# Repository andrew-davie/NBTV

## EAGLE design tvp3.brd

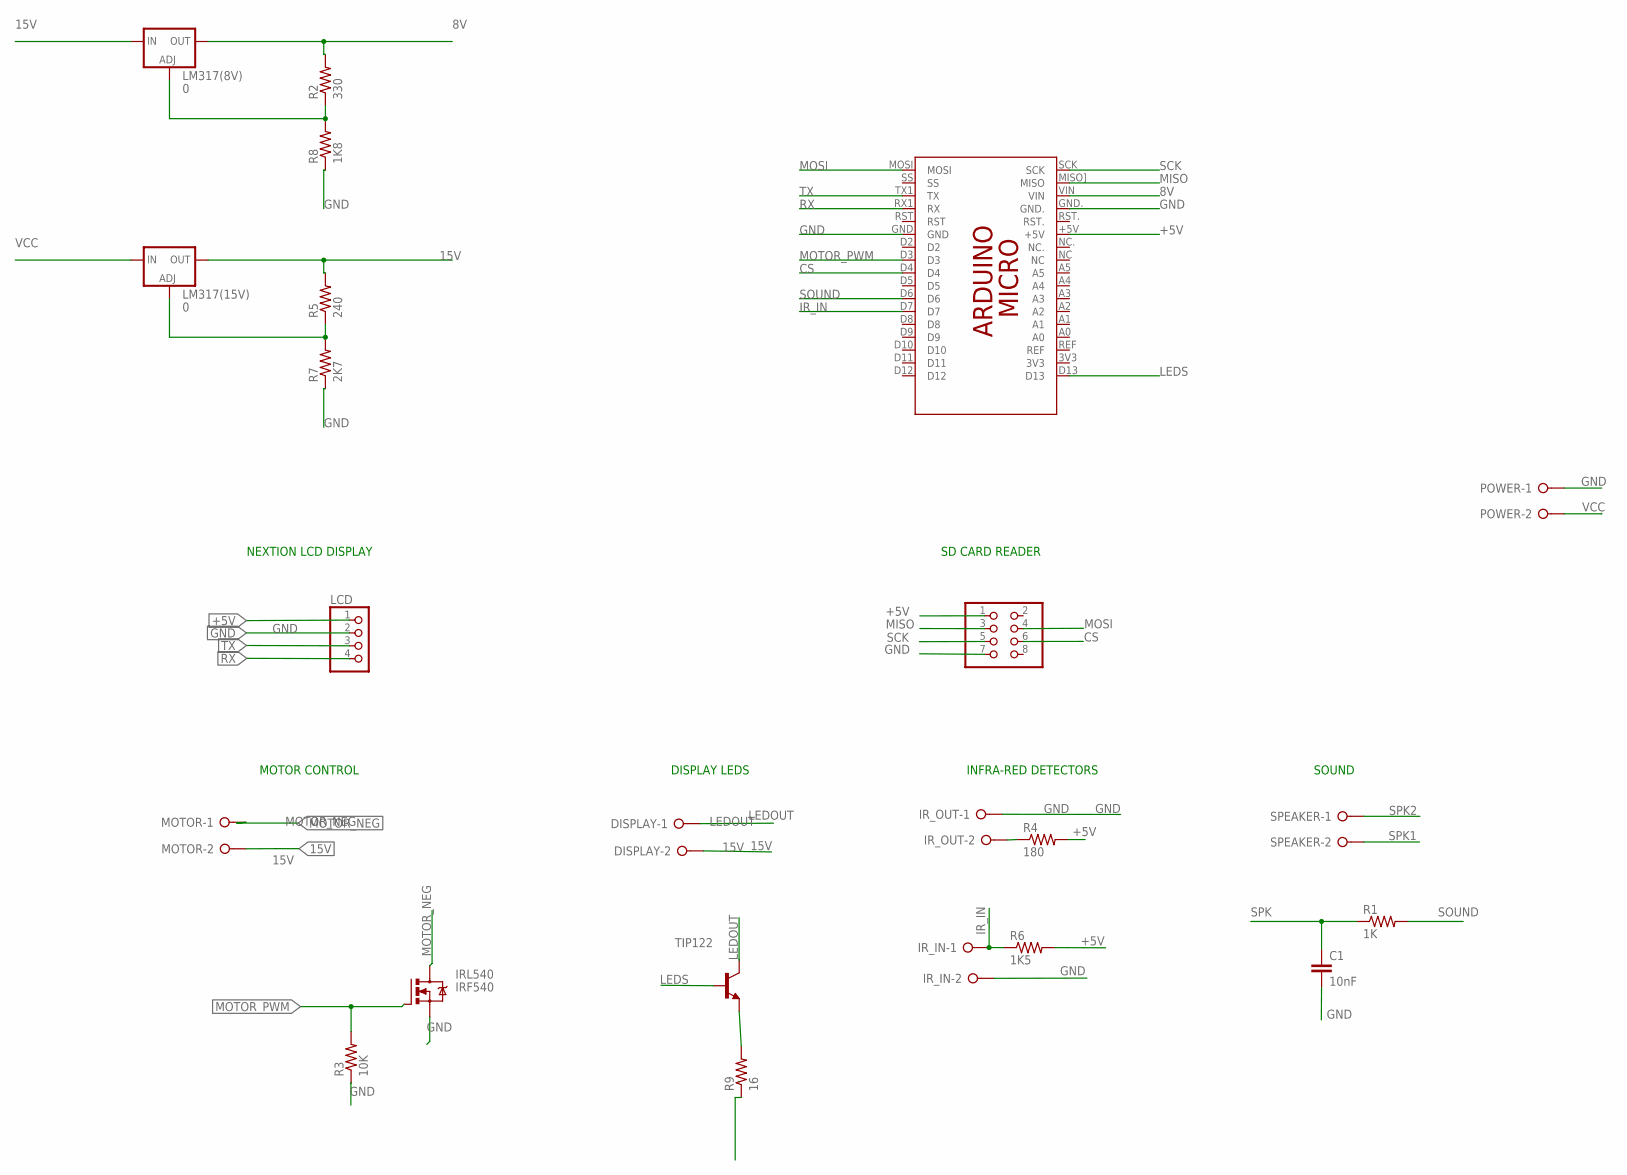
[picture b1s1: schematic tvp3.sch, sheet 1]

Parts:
C1: 10nF; C2.5-2
DISPLAY: W237-02P; W237-132
IRL540: IRF540; TO220BV
IR_IN: W237-02P; W237-132
IR_OUT: W237-02P; W237-132
LCD: PINHD-1X4; 1X04
LM317(8V), LM317(15V): 0; 317TS
MOTOR: W237-02P; W237-132
PCB2: ARDUINO_MICRO
POWER: W237-02P; W237-132
R1: 1K; 0207/10
R2: 330; 0207/10
R3: 10K; 0207/10
R4: 180; 0207/10
R5: 240; 0207/10
R6: 1K5; 0207/10
R7: 2K7; 0207/10
R8: 1K8; 0207/10
R9: 16; 0207/10
SPEAKER: W237-02P; W237-132
TIP122: -NPN-TO220V; TO220V
_: PINHD-2X4; 2X04

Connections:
8V: LM317(8V).2 (OUT), PCB2.VIN, R2.2
15V: DISPLAY.2, LM317(8V).3 (IN), LM317(15V).2 (OUT), MOTOR.2, R5.2
+5V: LCD.1, PCB2.+5V, R4.2, R6.2, _.1; also elsewhere on the board
CS: PCB2.D4, _.6
GND: C1.2, IRL540.S, IR_IN.2, IR_OUT.1, LCD.2, PCB2.GND, PCB2.GND., POWER.1, R3.1, R7.1, R8.1, R9.1, _.7; also elsewhere on the board
IR_IN: IR_IN.1, PCB2.D7, R6.1
IR_OUT: IR_OUT.2, R4.1
LEDOUT: DISPLAY.1, TIP122.2 (C)
LEDS: PCB2.D13, TIP122.1 (B)
MISO: PCB2.MISO] (MISO), _.3
MOSI: PCB2.MOSI, _.4
MOTOR_NEG: IRL540.D, MOTOR.1
MOTOR_PWM: IRL540.G, PCB2.D3, R3.2
unnamed: LM317(15V).1 (ADJ), R5.1, R7.2
unnamed: R9.2, TIP122.3 (E)
unnamed: LM317(8V).1 (ADJ), R2.1, R8.2
RX: LCD.4, PCB2.RX1 (RX)
SCK: PCB2.SCK, _.5
SOUND: PCB2.D6, R1.2
SPK: C1.1, R1.1; also elsewhere on the board
SPK1: SPEAKER.2; also elsewhere on the board
SPK2: SPEAKER.1; also elsewhere on the board
TX: LCD.3, PCB2.TX1 (TX)
VCC: LM317(15V).3 (IN), POWER.2

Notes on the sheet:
MOTOR CONTROL
DISPLAY LEDS
INFRA-RED DETECTORS
NEXTION LCD DISPLAY
SD CARD READER
SOUND

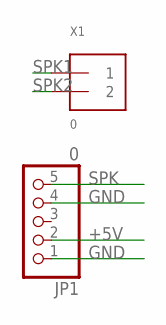
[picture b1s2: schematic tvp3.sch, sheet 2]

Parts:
JP1: 0; 1X05_ROUND_70
X1: 0; TERMBLOCK_1X2-3.5MM

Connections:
+5V: JP1.2; also elsewhere on the board
GND: JP1.1, JP1.4; also elsewhere on the board
SPK: JP1.5; also elsewhere on the board
SPK1: X1.1; also elsewhere on the board
SPK2: X1.2; also elsewhere on the board

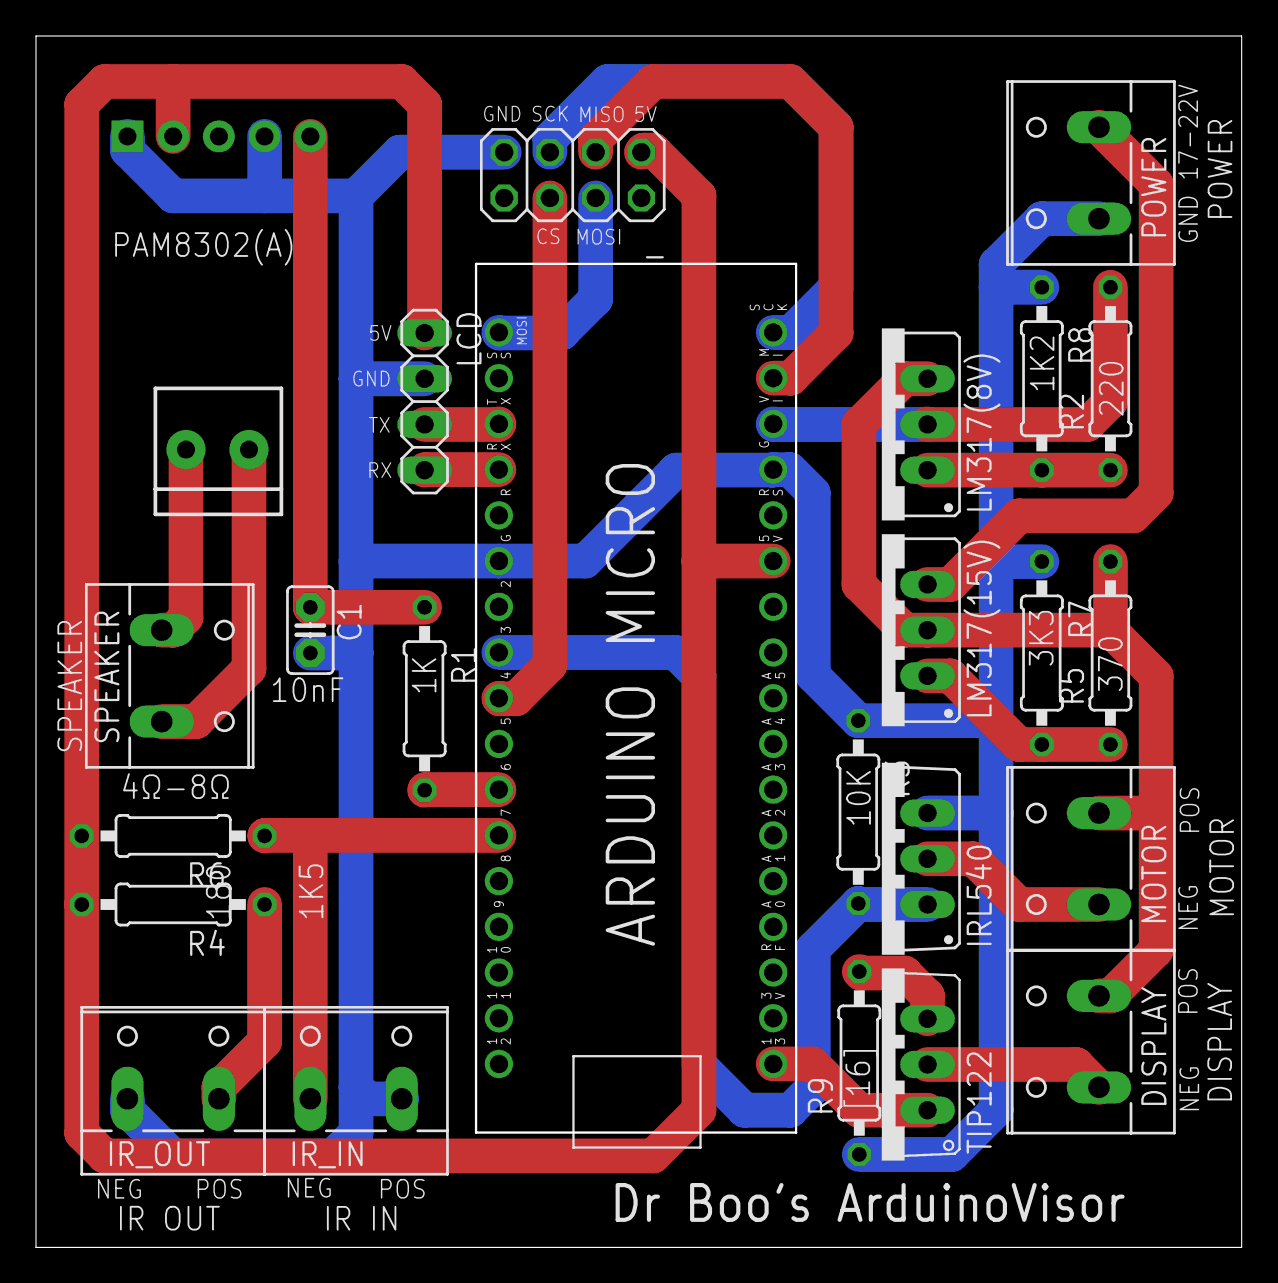
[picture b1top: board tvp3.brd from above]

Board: 2 copper layers, 67.0 x 67.3 mm, 25 parts (0 on the bottom side), 24 nets.

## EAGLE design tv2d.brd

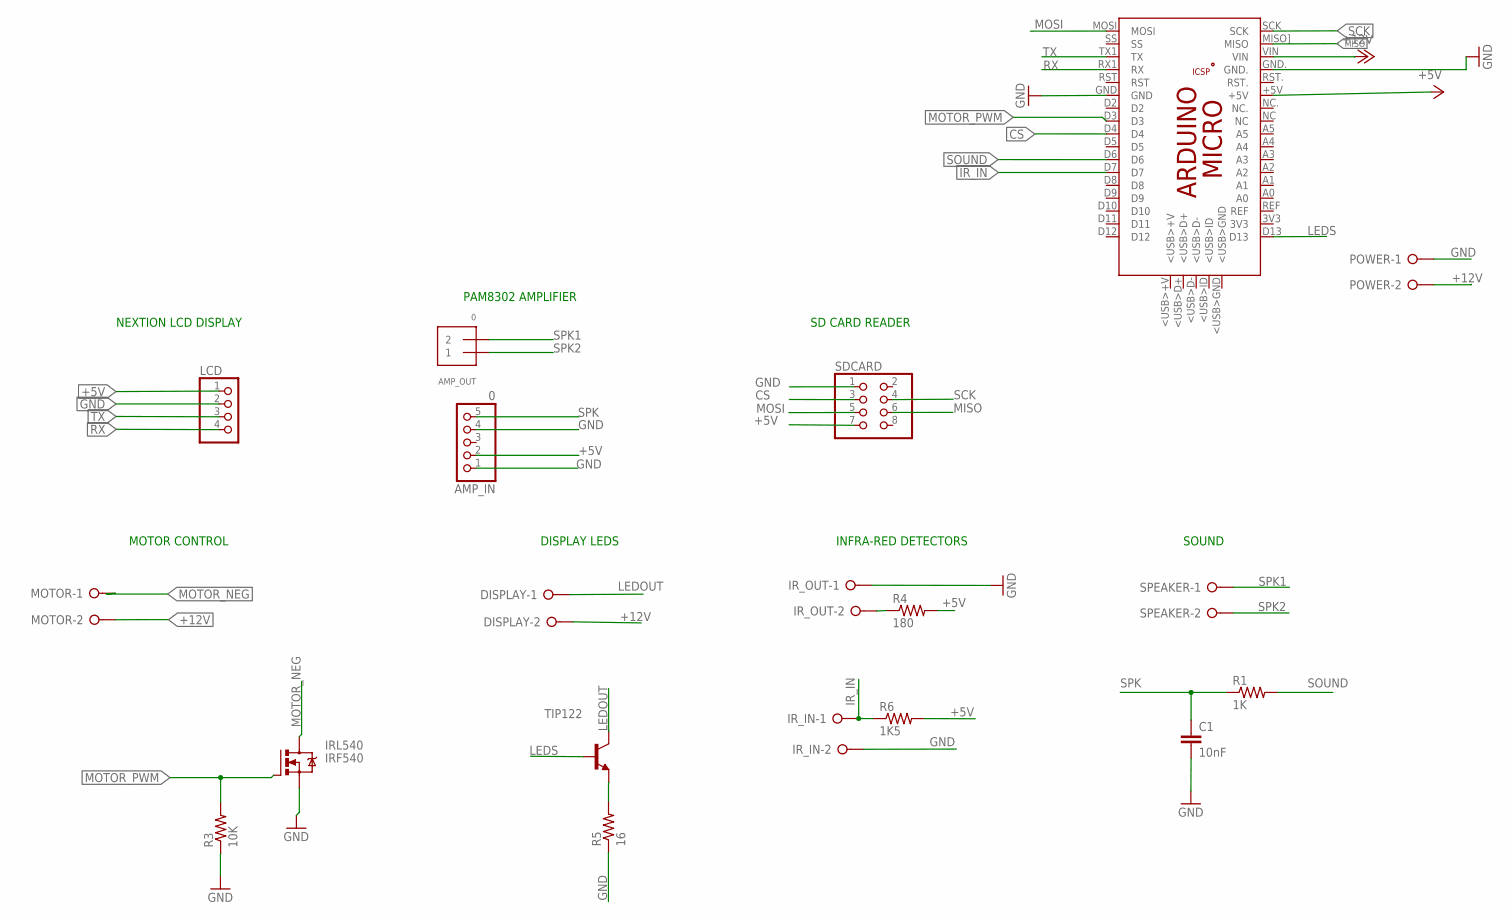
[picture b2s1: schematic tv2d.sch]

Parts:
AMP_IN: 0; 1X05_ROUND_70
AMP_OUT: 0; TERMBLOCK_1X2-3.5MM
C1: 10nF; C2.5-2
DISPLAY: W237-02P; W237-132
IRL540: IRF540; TO220BV
IR_IN: W237-02P; W237-132
IR_OUT: W237-02P; W237-132
LCD: PINHD-1X4; 1X04
MOTOR: W237-02P; W237-132
PCB1: ARDUINO_MICRO
POWER: W237-02P; W237-132
R1: 1K; 0207/10
R3: 10K; 0207/10
R4: 180; 0207/10
R5: 16; 0207/10
R6: 1K5; 0207/10
SDCARD: PINHD-2X4; 2X04
SPEAKER: W237-02P; W237-132
TIP122: -NPN-TO220V; TO220V

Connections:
+5V: AMP_IN.2, LCD.1, PCB1.+5V, R4.2, R6.2, SDCARD.7
+12V: DISPLAY.2, MOTOR.2, PCB1.VIN, POWER.2
CS: PCB1.D4, SDCARD.3
GND: AMP_IN.1, AMP_IN.4, C1.2, IRL540.S, IR_IN.2, IR_OUT.1, LCD.2, PCB1.GND, PCB1.GND., POWER.1, R3.1, R5.1, SDCARD.1
IR_IN: IR_IN.1, PCB1.D7, R6.1
IR_OUT: IR_OUT.2, R4.1
LEDOUT: DISPLAY.1, TIP122.2 (C)
LEDS: PCB1.D13, TIP122.1 (B)
MISO: PCB1.MISO] (MISO), SDCARD.6
MOSI: PCB1.MOSI, SDCARD.5
MOTOR_NEG: IRL540.D, MOTOR.1
MOTOR_PWM: IRL540.G, PCB1.D3, R3.2
unnamed: R5.2, TIP122.3 (E)
RX: LCD.4, PCB1.RX1 (RX)
SCK: PCB1.SCK, SDCARD.4
SOUND: PCB1.D6, R1.2
SPK: AMP_IN.5, C1.1, R1.1
SPK1: AMP_OUT.2, SPEAKER.1
SPK2: AMP_OUT.1, SPEAKER.2
TX: LCD.3, PCB1.TX1 (TX)

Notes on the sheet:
MOTOR CONTROL
DISPLAY LEDS
INFRA-RED DETECTORS
NEXTION LCD DISPLAY
PAM8302 AMPLIFIER
SD CARD READER
SOUND

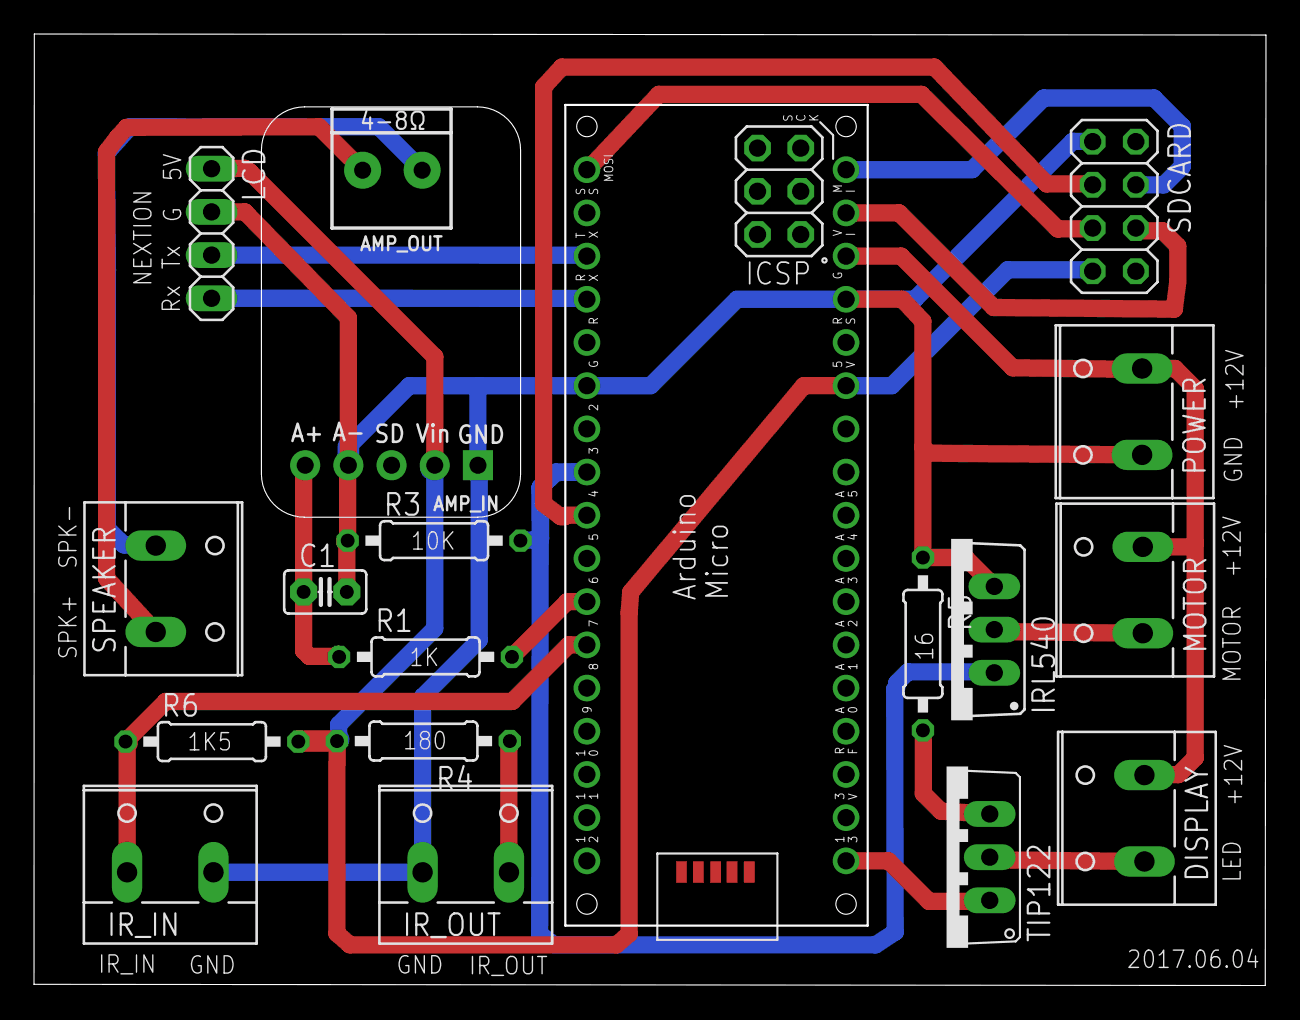
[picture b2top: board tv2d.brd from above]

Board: 2 copper layers, 72.4 x 55.9 mm, 19 parts (0 on the bottom side), 20 nets.

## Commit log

2017-03-10 first version
2017-03-25 let's get serious
    CIrcular streaming audio/video buffer implemented to reduce memory footprint
    my televisor is "pulling" and there must be a motor or disc bearing problem.
    PID operational but hardly able to resist the disturbance
    video streaming basically OK but occasonal glitching so there's a bug there somewhere
    SD card streaming good, but need a super-fast card, as we can't afford delays/lag
    rudimentary televisor operates OK off this code
2017-03-25 consolidation - prelminary
2017-03-25 cleaning for the great unwashed
2017-03-26 tidy up
2017-03-31 changed buffer handling
    playback pointer now absolute and continues regardless. Stream pointer also absolute, so calculation of bytes to stream is simple. The streaming might delay but will eventually catch up, and then the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
2017-04-01 gamma correction
2017-04-01 quadratic gamma correction from Klaas Robers
2017-04-04 8-bit video format, WAV loader rewrite
    now COmpatible with 16-bit and 8-bit NBTV files.
2017-04-05 some work on the Nextion interface
    lots of optimisation to reduce ram/memory
    fixed an off-by-one bug in the video playback (explains a few things)
    Nextion support works but clashes with playback - one or the other at the moment
    memory is short (RAM). May need to customise the libraries
2017-04-06 UI functional
    Moved video buffer stuffer to an interrupt, freeing up the main loop which now does the serial comms to the Nextion. This update has the 'brightness' control functional, taking slider values from the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
2017-04-10 functional frame lock
    First version demonstrating frame lock. Very slow and sensitive, but working!
2017-04-14 "solved" nextion RAM problem
    see NextionUI.cpp for comments - there appears to be an Arduino IDE linker problem.
2017-04-16 rationalisation
    Bug regarding circular buffer size - seems to occur when streaming from SD in chunks >64 bytes. Could be an overlap/clash in serial...?
2017-04-17 first functional audio
    last multi-file version - going to consolidate to single file soon
2017-04-17 consolidated to a single file + PID library
2017-04-17 another pass on optimise/cleanup
2017-04-21 PID working for 12.5Hz disc speed lock
2017-04-22 pixel-perfect framer!
    See https://www.youtube.com/watch?v=zXrc1Xl-fEc
2017-05-03 lots of nextion/optimisatino
    working on the file selection dialog
2017-05-03 added the Nextion design file for LCD UI
2017-05-03 added the Nextion LCD UI binary
2017-05-06 UI file selection dialog working
    Reworked the UI for the Nextion. Using callbacks instead of polling. Reworked TFT (Nextion binary). Still need to get "STOP" working, but nearly done. . See https://www.youtube.com/watch?time_continu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
2017-05-12 start/stop of tracks now working and synch correct
    Complete playback function now working with correct track synch and start/stop of motor and interrupts.
2017-05-19 generally working, now polishing
2017-05-19 generally working, now optimising
2017-05-21 clean, nearly complete
    Couple of issues
    * seeker not working properly
    * shifter not working properly
    This commit has cleaned up the TFT file a lot and managing the switching between INFO/SHIFT screen nicely
2017-06-04 eagle files for stand-alone circuit board
    Untested as yet! I'm also learning how to use Eagle, so it might be a bit weird in places :)
2017-06-16 eagle board/schematic for LED matrix display
2017-06-16 source files for nextion library
    I've made some mods so here's a copy of my local nextion library
    specifically, the default baud rate is 115200 and some other minor changes
2017-06-16 stand-alone
    This version will play all files on the SD card, in the case where NO Nextion is included
    That is, when NEXTION is not defined in the code - the televisor will still play stuff
2017-06-16 baud rate default 115200
2017-06-16 default baud 115200
2017-06-16 sample NBTV8-format file for playback
    Doctor Who episode, complete, in NBTV8 format
    also includes accompanying info file for UI display
2017-07-02 added new circuit board
    Version 2 of circuit board
2017-07-06 corrected version upload
2017-08-06 moved to Atom IDE
    some updates to fix sound 'popping'
    code now run through auto-formatter
2017-08-06 test
2017-10-15 ugrading to keith colson's revisions
2017-10-16 optimisations
2017-10-17 optimisations
    Completely untested! Could be broken. Just wanted to get this stage captured for posterity.
    There seemed to be a bug in the seek, which I've fixed. No idea how it managed to work before - but *actually* I realised this may actually explain the half-frame issue I'vebeen seeing after seeking.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
2017-10-17 optimisatoin
    dumb me updated the files to the root directory before. These are now correct.
    Many optimisations, completely untested.
    One major bug found (?) in the seeking - perhaps this explains the half-frames I've occasionally seen. The header size was not taken into account when seeking, so it would have been "out" by that amo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
2017-10-19 fixed the broken sound. hopefully.
    Just did a diff, not sure what actually fixed the sound. Appears to work.
2017-10-19 starting to decouple hardwired NBTV8 code
    Let's see if we can get this baby working on 44.1KHz again...
    Started to remove the hardwired magic numbers that tied the operation to 19.2KHz.
2017-10-19 optimisation
    Removed volatiles. Seems to make no difference, except for hundreds of bytes saved.
    Some speedups in the playback interrupt. Used smaller type for audio.
2017-10-20 optimisations
    saved some memory. playback interrupt slightly quicker.

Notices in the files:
parts and their libraries:
microbuilder: This work is placed in the public domain, and may be freely used for commercial and non-commercial work with the following conditions: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
